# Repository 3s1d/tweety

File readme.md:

# Skytraxx Tweety
A low-cost audio-only variometer which is fully open hardware/source and Arduino compatible.
It uses a [MS5637](http://www.mouser.com/new/measurement-specialties/measurement-specialties-ms5637/) pressure sensor in combination with [Linear Regression](https://en.wikipedia.org/wiki/Linear_regression) to estimate the current climb rate. All the computations are done on an Atmel [Attiny88](http://www.atmel.com/devices/ATTINY88.aspx). The CR2450 battery should last a whole season...

You can build it on your own or buy it in our [shop](https://www.skytraxx.eu/shop?product_id=290) and modify it as you like.

## Operation

### Turn on
Press the button until you here a short beep. Release the button within in 1 second and Tweety turns on. You will here the welcome sound, followed by 0.5 sec pause and the battery state:
- 2 beeps: Battery is good
- 1 beep: Battery is okay
- no beep: You should consider changing the battery

### Turn off
Press the button until you hear the bye sound. Release the button.

### Auto-off
Tweety will shutdown itself if in the past 30 min all climb rate were within -0.8 m/s to 0.8 m/s.

### Configuration
The sink tone can be switched on or off.
Remove the battery. Press and hold the button while re-inserting the coin cell. Release the button. 
- 2 beeps: Sink tone on
- 1 beep: Sink tone off

A short press changes the settings. Use long press (4 sec.) to store the setting and to enter the normal operation mode again.

## Settings
See `climb.h`
- Climb threshold: > 0.3m/s
- Sink threshold: < -2.5m/s
- Averaging interval: 1.5 sec

If you want to change those settings or change the vario tone profile (`piezo.c`), you need to recompile and upload the sources.

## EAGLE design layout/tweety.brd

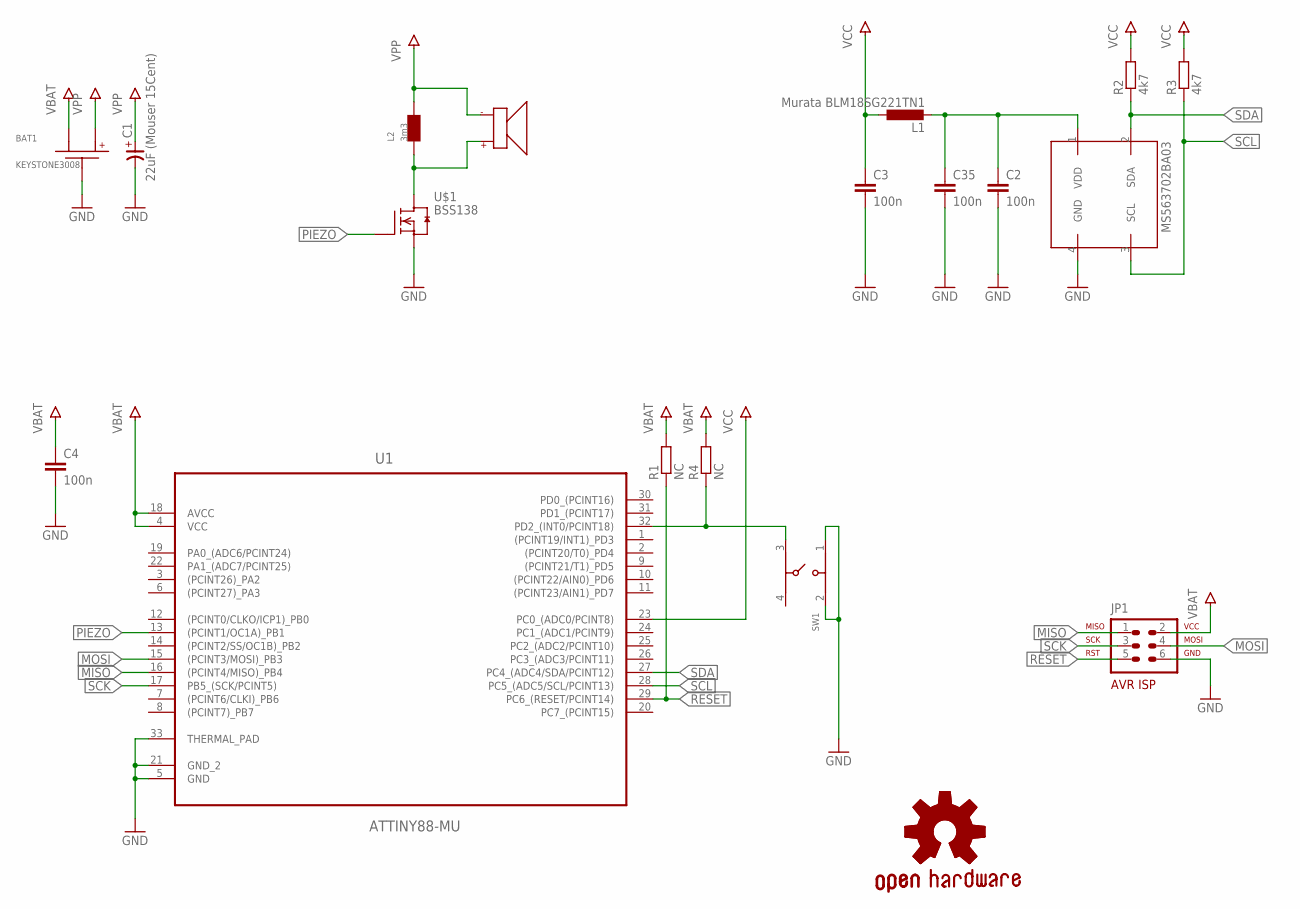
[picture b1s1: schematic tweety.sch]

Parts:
BAT1: KEYSTONE3008
C1: 22uF (Mouser 15Cent); 3528-21R/T
C2, C3, C4, C35: 100n; C0603
GOLD_ORB_SM1: OSHWLOGO_GOLD_ORB_MED; OSHW1
IC2: MS563702BA03; MS5637
JP1: AVR-ISP-6VERT; AVR-ISP-6
L1: Murata BLM18SG221TN1; L0603
L2: 3m3; SDR0503
P2: PKLCS1212E2400; PKLCS1212
R1, R4: NC; R0603
R2, R3: 4k7; R0603
SW1: 4301X20858X6
U1: ATTINY88-MU; QFN50P500X500X100-33N
U$1: BSS138; SOT23

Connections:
GND: BAT1.N, C1.-, C2.2, C3.2, C4.2, C35.2, IC2.4 (GND), JP1.6, SW1.1, SW1.2, U1.5 (GND), U1.21 (GND_2), U1.33 (THERMAL_PAD), U$1.2 (S)
MISO: JP1.1, U1.16 ((PCINT4/MISO)_PB4)
MOSI: JP1.4, U1.15 ((PCINT3/MOSI)_PB3)
unnamed: C2.1, C35.1, IC2.1 (VDD), L1.2
unnamed: R4.1, SW1.3, U1.32 (PD2_(INT0/PCINT18))
unnamed: L2.P$1, P2.P$+, U$1.3 (D)
PIEZO: U1.13 ((PCINT1/OC1A)_PB1), U$1.1 (G)
RESET: JP1.5, R1.1, U1.29 (PC6_(RESET/PCINT14))
SCK: JP1.3, U1.17 (PB5_(SCK/PCINT5))
SCL: IC2.3 (SCL), R3.1, U1.28 (PC5_(ADC5/SCL/PCINT13))
SDA: IC2.2 (SDA), R2.1, U1.27 (PC4_(ADC4/SDA/PCINT12))
VBAT: BAT1.P$3 (P1), C4.1, JP1.2, R1.2, R4.2, U1.4 (VCC), U1.18 (AVCC)
VCC: C3.1, L1.1, R2.2, R3.2, U1.23 (PC0_(ADC0/PCINT8))
VPP: BAT1.P$4 (P2), C1.+, L2.P$2, P2.P$-

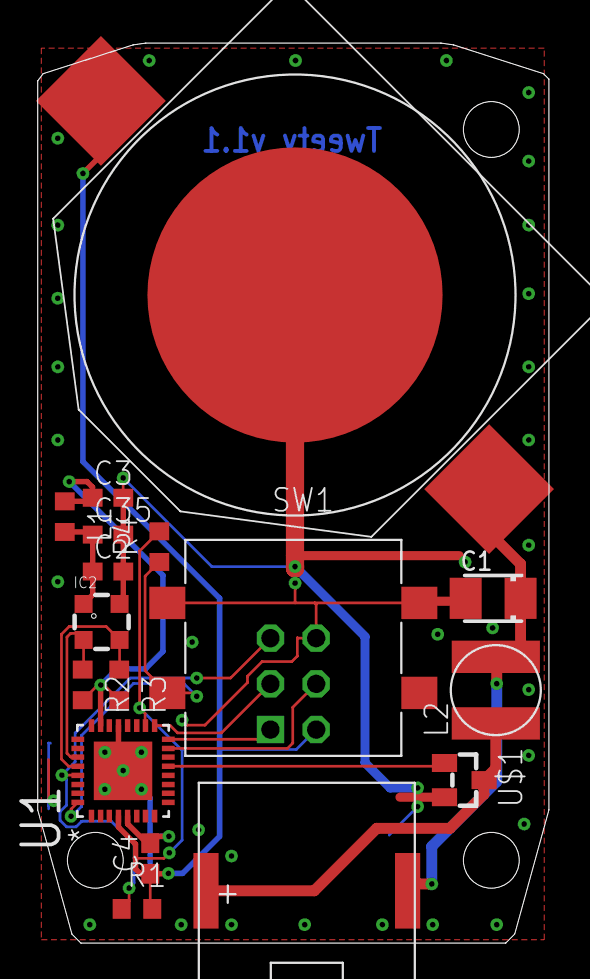
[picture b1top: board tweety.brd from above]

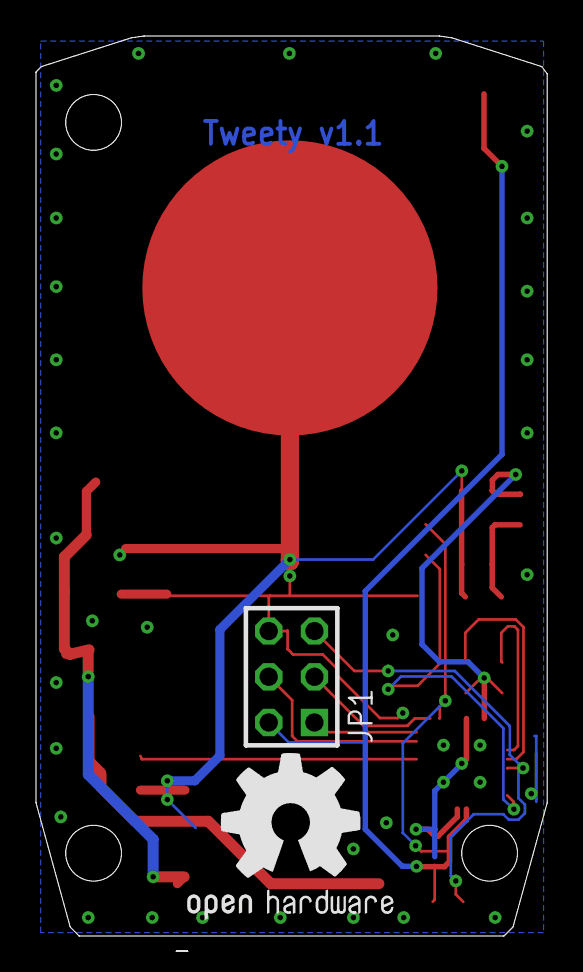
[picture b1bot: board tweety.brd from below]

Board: 2 copper layers, 28.4 x 50.0 mm, 19 parts (2 on the bottom side), 14 nets.

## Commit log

2016-06-11 pcb init
2016-06-29 initial layout
2016-07-17 v0.2
2016-07-31 mount added
2016-07-31 initial version
2016-07-31 initial complexity
2016-07-31 added missing files
2016-07-31 debug interface added
2016-08-01 some presure corrections
2016-08-01 prior a newtwi driver
2016-08-01 first usable results
2016-08-01 added missing file
2016-08-01 value clibm values
2016-08-01 added some todos
2016-08-01 mount revised
2016-08-02 introduced test climb API; LR_def solved using defines -> saved 200bytes of flash
2016-08-02 comment added
2016-08-02 introduced sleep api
2016-08-02 aquidistant sensor distances
2016-08-02 power on/off
2016-08-02 battery evaluation added
2016-08-03 test
2016-08-03 climb rate becomes a global variable
2016-08-03 comments added
2016-08-03 config
2016-08-03 intorduced climb routine
2016-08-03 beep interface working. everything complete, except beeping :)
2016-08-03 removed som coemments
2016-08-04 v1.0
2016-08-04 erster piepsversuch
2016-08-04 like skybean
2016-08-04 float 2 int
2016-08-04 remove m=round...
2016-08-04 u64 2 u32
2016-08-04 profil and bugfix
2016-08-04 profil
2016-08-04 optimierung
2016-08-05 set averaging to 1.5sec. cleaned piepsen_on_off
2016-08-05 bumped up volumne, again
2016-08-05 must be tested in flight
2016-08-05 some cosmetics
2016-08-05 disabled debug
2016-08-05 slightly improved power on feedback
2016-08-05 new profil (skybean configurator)
2016-08-06 aktuell
2016-08-06 read/write eeprom seems to be broken with avrlibc-2.0.0, doing it manually
2016-08-07 removed sinkthreadhold 'extrawurst'
2016-08-07 some more cleanup
2016-08-08 auto switch off
2016-08-08 get_near bug fixed
2016-08-08 small cosmetic
2016-08-08 some more cosmetrics :)
2016-08-09 added missinf file
2016-09-12 very aggressiv battery states
2016-09-13 manual added
2016-09-13 picture added
2016-09-13 readmed added
2016-09-13 redesgined
2016-09-13 auto off added
2016-09-13 added shop link
2016-10-03 improved poweron
2016-10-03 new pressur enging, still not working for cold temperatures
2016-10-04 'cold' bugfix
2016-10-04 docu update
2016-10-04 30min power off @ 2Mhz
2016-10-31 layout optimized

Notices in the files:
parts and their libraries:
freetronics-original: Licensing: CC v3.0 Share-Alike You are welcome to use this library for commercial purposes.
EAGLE-TACT_SWITCHES-rev1: Copyright: Würth Elektronik
m-pad-1.5: License : GNU General Public License version 2 (see bottom)
